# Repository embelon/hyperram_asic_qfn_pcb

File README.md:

# hyperram_asic_qfn_pcb
Test PCB for CARAVEL ASIC (in QFP package) manufactured by efables.com in Open Source Shuttles to check HyperRAM memory controller IP connected to RISC-V through Wishbone bus.

HyperRAM controller was submitted in [GFMPW-0 (5V)](https://platform.efabless.com/projects/1667) and [MPW-8](https://platform.efabless.com/projects/1826).

HyperRAM controller IP was created to work with Cypress S27KL0641:
https://github.com/embelon/wb_hyperram

### Images

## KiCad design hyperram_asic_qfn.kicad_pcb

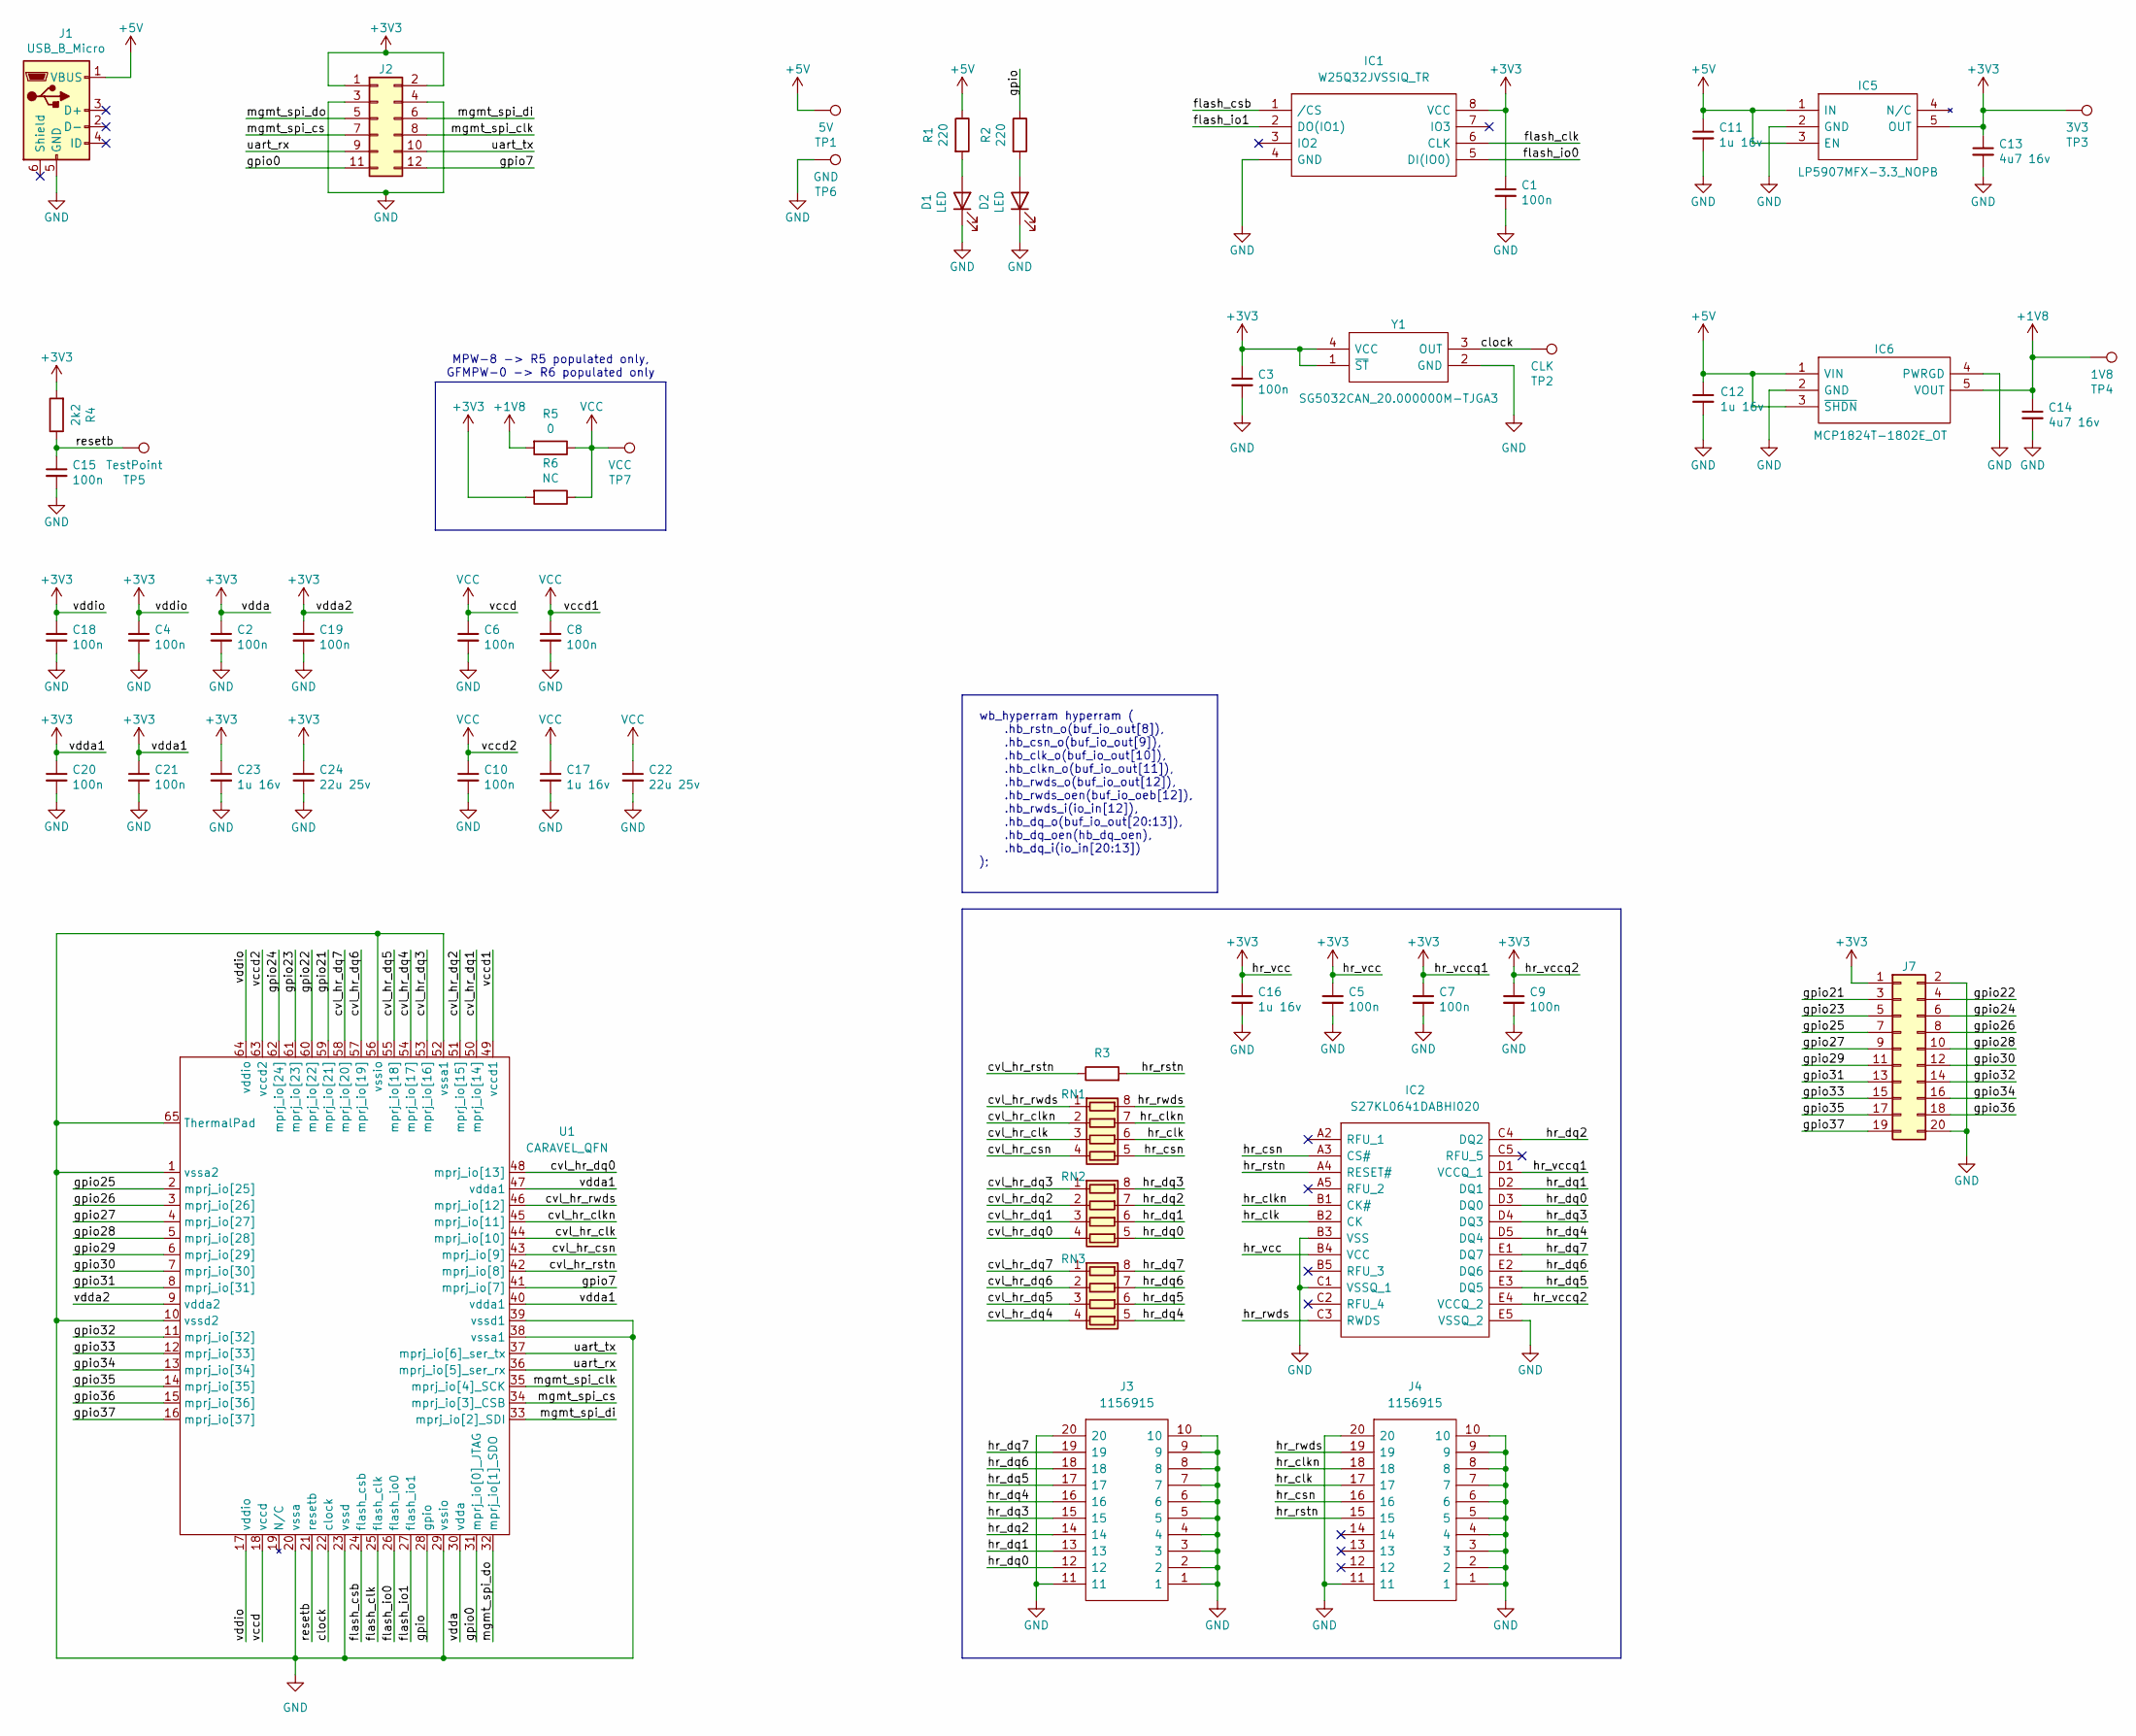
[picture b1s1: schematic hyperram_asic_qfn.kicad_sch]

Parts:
C1, C2, C3, C4, C5, C6, C7, C8, C9, C10, C15, C19, C20, C21: 100n; C_0402_1005Metric_Pad0.74x0.62mm_HandSolder; Part CGA3E2X7R1H223K080AA
C11, C12, C16, C17, C23: 1u 16v; C_0805_2012Metric_Pad1.18x1.45mm_HandSolder; Part CL10A105KO8NNNC
C13, C14: 4u7 16v; C_0805_2012Metric_Pad1.18x1.45mm_HandSolder; Part CC0603KRX5R7BB475
C18: 100n; C_0402_1005Metric_Pad0.74x0.62mm_HandSolder; Part CL10A105KO8NNNC
C22, C24: 22u 25v; C_0805_2012Metric_Pad1.18x1.45mm_HandSolder; Part CL10A105KO8NNNC
D1, D2: LED; LED_0805_2012Metric_Pad1.15x1.40mm_HandSolder; Part LS Q976-NR-1
IC1: W25Q32JVSSIQ_TR; SOIC127P790X216-8N; Mouser Part Number 454-W25Q32JVSSIQTR
IC2: S27KL0641DABHI020; BGA24C100P5X5_600X800X100; Manufacturer_Part_Number S27KL0641DABHI020; Mouser Part Number 727-S27KL0641DABHI02
IC5: LP5907MFX-3.3_NOPB; SOT95P280X145-5N; Mouser Part Number 595-LP5907MFX-3.3NPB
IC6: MCP1824T-1802E_OT; SOT95P270X145-5N; Mouser Part Number 579-MCP1824T-1802EOT
J1: USB_B_Micro; UJ2MIBHGSMTTR; Part 105017-0001
J2: Conn_02x06_Odd_Even; PinHeader_2x06_P2.54mm_Vertical
J3, J4: 1156915; Mouser Part Number 651-1156915
J7: Conn_02x10_Odd_Even; PinHeader_2x10_P2.54mm_Vertical
R1, R2: 220; R_0603_1608Metric; Part ‎RC0603JR-07100RL‎
R3: R; R_0603_1608Metric
R4: 2k2; R_0603_1608Metric; Part ‎RC0603JR-07100RL‎
R5: 0; R_0603_1608Metric; Part ‎RC0603JR-07100RL‎
R6: NC; R_0603_1608Metric; Part ‎RC0603JR-07100RL‎
RN1, RN2, RN3: CAY16-22R0F4LF; CAY16000J4LF
TP1: 5V; TestPoint_Pad_D1.0mm
TP2: CLK; TestPoint_Pad_D1.0mm
TP3: 3V3; TestPoint_Pad_D1.0mm
TP4: 1V8; TestPoint_Pad_D1.0mm
TP5: TestPoint; TestPoint_Pad_D1.0mm
TP6: GND; TestPoint_Pad_D1.0mm
TP7: VCC; TestPoint_Pad_D1.0mm
U1: CARAVEL_QFN; QFN-64-1EP_9x9mm_P0.5mm_EP7.65x7.65mm
Y1: SG5032CAN_20.000000M-TJGA3; SG5032CAN20000000MTJGA3; Mouser Part Number 732-5032CAN20.0TJGA3

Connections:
+1V8: C14.1, IC6.5 (VOUT), R5.2, TP4.1
+3V3: C1.1, C2.1, C3.1, C4.1, C5.1, C7.1, C9.1, C13.1, C16.1, C18.1, C19.1, C20.1, C21.1, C23.1, C24.1, IC1.8 (VCC), IC2.B4 (VCC), IC2.D1 (VCCQ_1), IC2.E4 (VCCQ_2), IC5.5 (OUT), J2.1, J2.2, J7.1, R4.2, R6.2, TP3.1, U1.9 (vdda2), U1.17 (vddio), U1.30 (vdda), U1.40 (vdda1), U1.47 (vdda1), U1.64 (vddio), Y1.1 (~ST), Y1.4 (VCC)
+5V: C11.1, C12.1, IC5.1 (IN), IC5.3 (EN), IC6.1 (VIN), IC6.3 (~SHDN), J1.1 (VBUS), R1.1, TP1.1
/clock: TP2.1, U1.22 (clock), Y1.3 (OUT)
/cvl_hr_clk: RN1.3 (R3.1), U1.44 (mprj_io[10])
/cvl_hr_clkn: RN1.2 (R2.1), U1.45 (mprj_io[11])
/cvl_hr_csn: RN1.4 (R4.1), U1.43 (mprj_io[9])
/cvl_hr_dq0: RN2.4 (R4.1), U1.48 (mprj_io[13])
/cvl_hr_dq1: RN2.3 (R3.1), U1.50 (mprj_io[14])
/cvl_hr_dq2: RN2.2 (R2.1), U1.51 (mprj_io[15])
/cvl_hr_dq3: RN2.1 (R1.1), U1.53 (mprj_io[16])
/cvl_hr_dq4: RN3.4 (R4.1), U1.54 (mprj_io[17])
/cvl_hr_dq5: RN3.3 (R3.1), U1.55 (mprj_io[18])
/cvl_hr_dq6: RN3.2 (R2.1), U1.57 (mprj_io[19])
/cvl_hr_dq7: RN3.1 (R1.1), U1.58 (mprj_io[20])
/cvl_hr_rstn: R3.1, U1.42 (mprj_io[8])
/cvl_hr_rwds: RN1.1 (R1.1), U1.46 (mprj_io[12])
/flash_clk: IC1.6 (CLK), U1.25 (flash_clk)
/flash_csb: IC1.1 (/CS), U1.24 (flash_csb)
/flash_io0: IC1.5 (DI(IO0)), U1.26 (flash_io0)
/flash_io1: IC1.2 (DO(IO1)), U1.27 (flash_io1)
/gpio: R2.1, U1.28 (gpio)
/gpio0: J2.11, U1.31 (mprj_io[0]_JTAG)
/gpio7: J2.12, U1.41 (mprj_io[7])
/gpio21: J7.3, U1.59 (mprj_io[21])
/gpio22: J7.4, U1.60 (mprj_io[22])
/gpio23: J7.5, U1.61 (mprj_io[23])
/gpio24: J7.6, U1.62 (mprj_io[24])
/gpio25: J7.7, U1.2 (mprj_io[25])
/gpio26: J7.8, U1.3 (mprj_io[26])
/gpio27: J7.9, U1.4 (mprj_io[27])
/gpio28: J7.10, U1.5 (mprj_io[28])
/gpio29: J7.11, U1.6 (mprj_io[29])
/gpio30: J7.12, U1.7 (mprj_io[30])
/gpio31: J7.13, U1.8 (mprj_io[31])
/gpio32: J7.14, U1.11 (mprj_io[32])
/gpio33: J7.15, U1.12 (mprj_io[33])
/gpio34: J7.16, U1.13 (mprj_io[34])
/gpio35: J7.17, U1.14 (mprj_io[35])
/gpio36: J7.18, U1.15 (mprj_io[36])
/gpio37: J7.19, U1.16 (mprj_io[37])
/hr_clk: IC2.B2 (CK), J4.17, RN1.6 (R3.2)
/hr_clkn: IC2.B1 (CK#), J4.18, RN1.7 (R2.2)
/hr_csn: IC2.A3 (CS#), J4.16, RN1.5 (R4.2)
/hr_dq0: IC2.D3 (DQ0), J3.12, RN2.5 (R4.2)
/hr_dq1: IC2.D2 (DQ1), J3.13, RN2.6 (R3.2)
/hr_dq2: IC2.C4 (DQ2), J3.14, RN2.7 (R2.2)
/hr_dq3: IC2.D4 (DQ3), J3.15, RN2.8 (R1.2)
/hr_dq4: IC2.D5 (DQ4), J3.16, RN3.5 (R4.2)
/hr_dq5: IC2.E3 (DQ5), J3.17, RN3.6 (R3.2)
/hr_dq6: IC2.E2 (DQ6), J3.18, RN3.7 (R2.2)
/hr_dq7: IC2.E1 (DQ7), J3.19, RN3.8 (R1.2)
/hr_rstn: IC2.A4 (RESET#), J4.15, R3.2
/hr_rwds: IC2.C3 (RWDS), J4.19, RN1.8 (R1.2)
/mgmt_spi_clk: J2.8, U1.35 (mprj_io[4]_SCK)
/mgmt_spi_cs: J2.7, U1.34 (mprj_io[3]_CSB)
/mgmt_spi_di: J2.6, U1.33 (mprj_io[2]_SDI)
/mgmt_spi_do: J2.5, U1.32 (mprj_io[1]_SDO)
/resetb: C15.1, R4.1, TP5.1, U1.21 (resetb)
/uart_rx: J2.9, U1.36 (mprj_io[5]_ser_rx)
/uart_tx: J2.10, U1.37 (mprj_io[6]_ser_tx)
GND: C1.2, C2.2, C3.2, C4.2, C5.2, C6.2, C7.2, C8.2, C9.2, C10.2, C11.2, C12.2, C13.2, C14.2, C15.2, C16.2, C17.2, C18.2, C19.2, C20.2, C21.2, C22.2, C23.2, C24.2, D1.1 (K), D2.1 (K), IC1.4 (GND), IC2.B3 (VSS), IC2.C1 (VSSQ_1), IC2.E5 (VSSQ_2), IC5.2 (GND), IC6.2 (GND), IC6.4 (PWRGD), J1.5 (GND), J2.3, J2.4, J3.1, J3.2, J3.3, J3.4, J3.5, J3.6, J3.7, J3.8, J3.9, J3.10, J3.11, J3.20, J4.1, J4.2, J4.3, J4.4, J4.5, J4.6, J4.7, J4.8, J4.9, J4.10, J4.11, J4.20, J7.2, J7.20, TP6.1, U1.1 (vssa2), U1.10 (vssd2), U1.20 (vssa), U1.23 (vssd), U1.29 (vssio), U1.38 (vssa1), U1.39 (vssd1), U1.52 (vssa1), U1.56 (vssio), U1.65 (ThermalPad), Y1.2 (GND)
unnamed: D1.2 (A), R1.2
unnamed: D2.2 (A), R2.2
VCC: C6.1, C8.1, C10.1, C17.1, C22.1, R5.1, R6.1, TP7.1, U1.18 (vccd), U1.49 (vccd1), U1.63 (vccd2)

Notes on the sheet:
MPW-8 -> R5 populated only, GFMPW-0 -> R6 populated only
wb_hyperram hyperram ( .hb_rstn_o(buf_io_out[8]), .hb_csn_o(buf_io_out[9]), .hb_clk_o(buf_io_out[10]), .hb_clkn_o(buf_io_out[11]), .hb_rwds_o(buf_io_out[12]), .hb_rwds_oen(buf_io_oeb[12]), .hb_rwds_i(io_in[12]), .hb_dq_o(buf_io_out[20:13]), .hb_dq_oen(hb_dq_oen), .hb_dq_i(io_in[20:13]) );

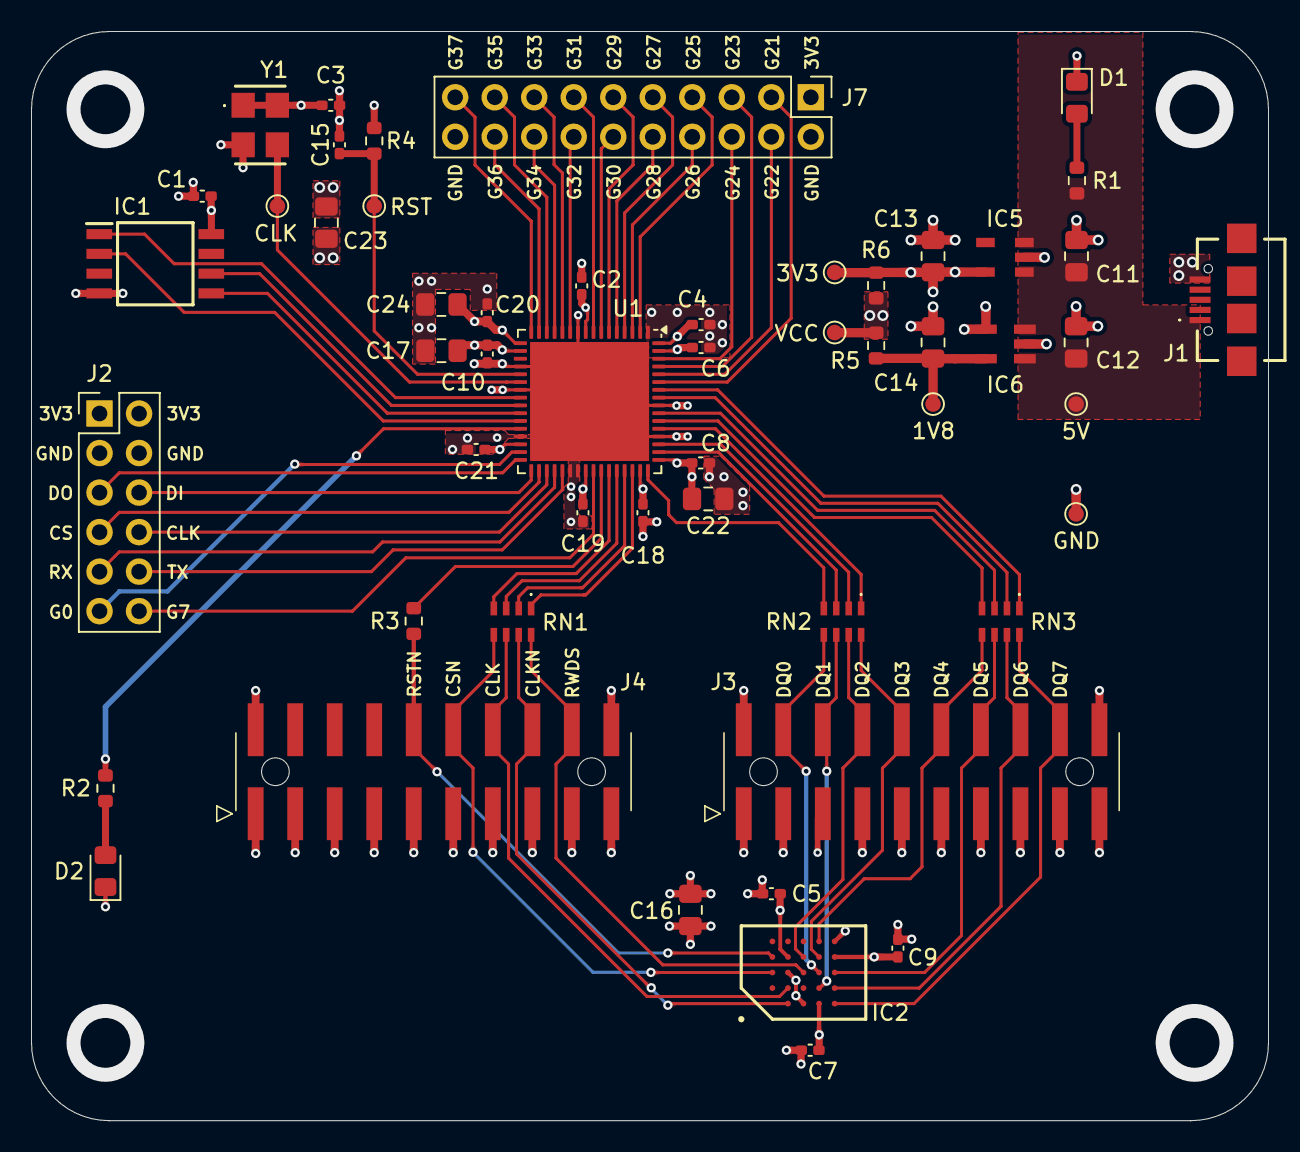
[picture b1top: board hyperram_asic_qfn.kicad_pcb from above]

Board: 4 copper layers, 79.5 x 70.0 mm, 53 parts (0 on the bottom side), 65 nets.

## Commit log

2024-04-26 Updated schematic with symbol CARAVEL WLCSP changed to CARAVEL QFN
2024-04-27 Added GPIO header. Cleaned up ERC warnings and errors in schematic.
2024-04-28 Updated schematic: resistors instead of jumpers to select VCC, integrated two smaller headers into one bigger.
2024-04-28 Fixed package assignments and library. Reordered signals to easy routing pcb.
2024-04-28 First try on component placement and routing.
2024-05-05 Changed design constraints to adjust to PCBWay and JLCPCB abilities for Standard 4-layer boards.
2024-05-05 Removed duplicated LDOs in BGA packages.
2024-05-05 Adjusted placement of some components and started routing tracks between ASIC and HyperRAM chip.
2024-05-07 First try for routing digital signals (DSPI, GPIOs, CLK, RST)
2024-05-09 Improved placement. Routed all digital signals.
2024-05-11 All signals routed, polygons filled.
2024-05-11 Updated USB footprint, Through Hole to SMD
2024-05-11 Fixed PCB DRC issues - prepared for PCBWay, track/spacing 4/4mils, min hole size 0.25mm
2024-05-11 Updated Testpoints description to voltage values.
2024-05-11 Adjusted References on Silkscreen for better readability
2024-05-12 Fixed position of USB connector
2024-05-30 Added missing resistance value for R3
2024-05-30 Created BOM
2024-06-11 Added render action for PCB
